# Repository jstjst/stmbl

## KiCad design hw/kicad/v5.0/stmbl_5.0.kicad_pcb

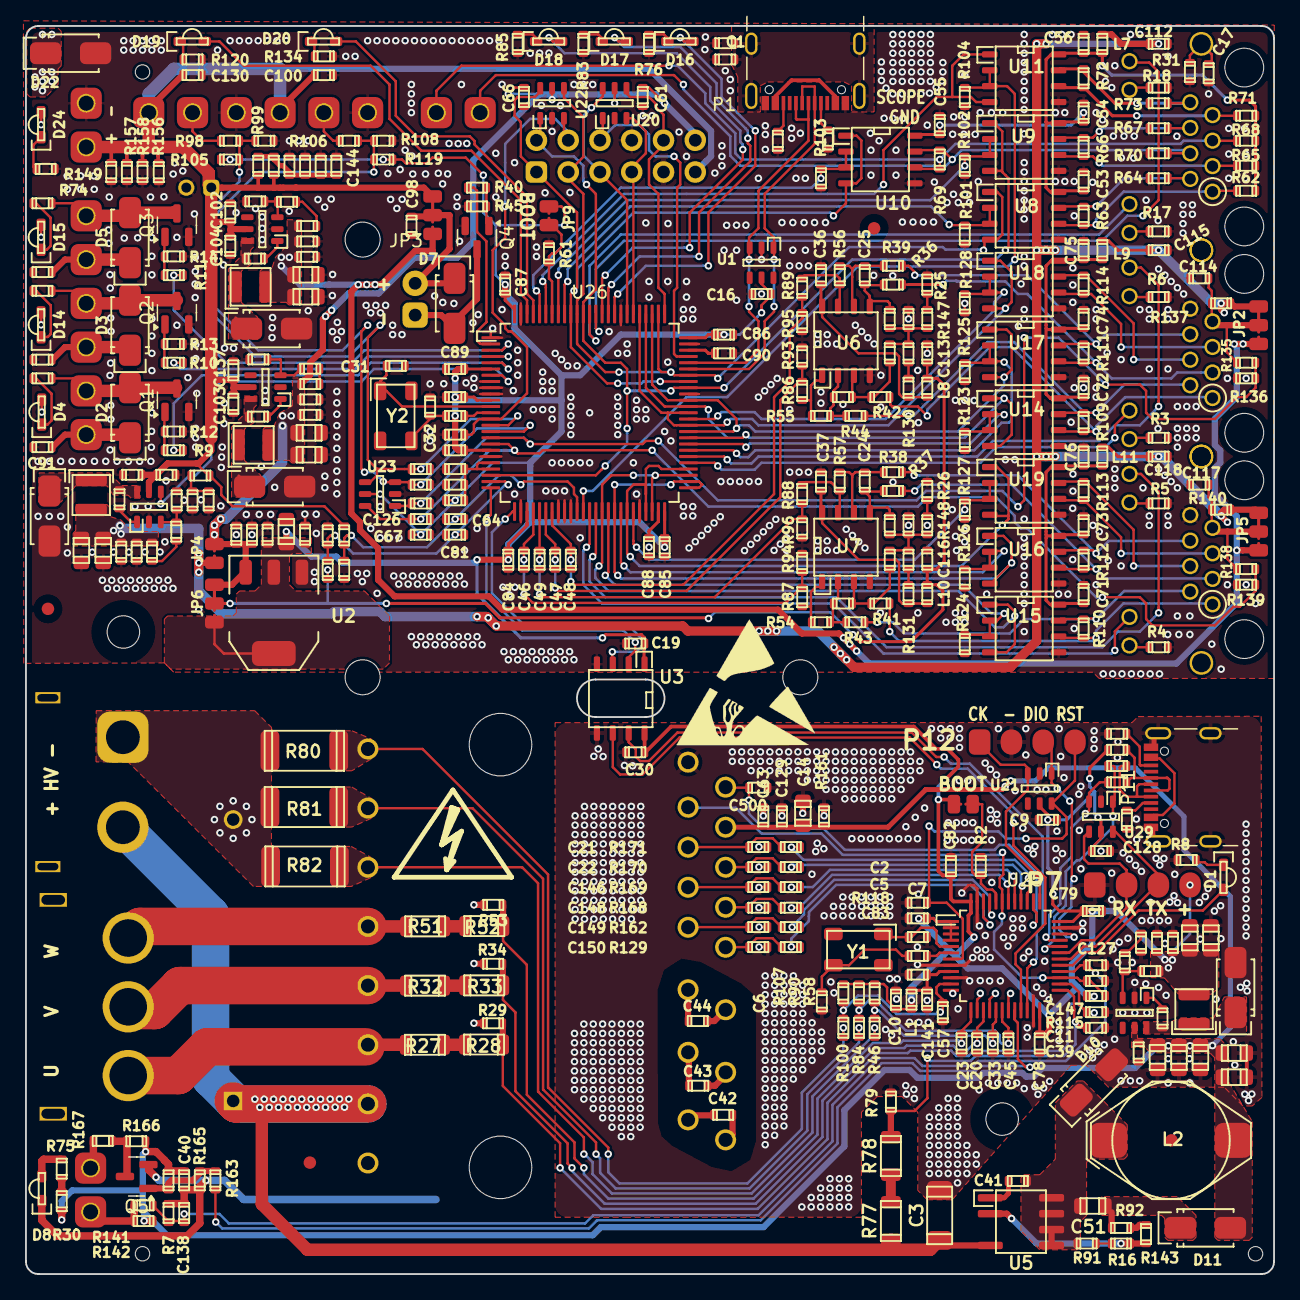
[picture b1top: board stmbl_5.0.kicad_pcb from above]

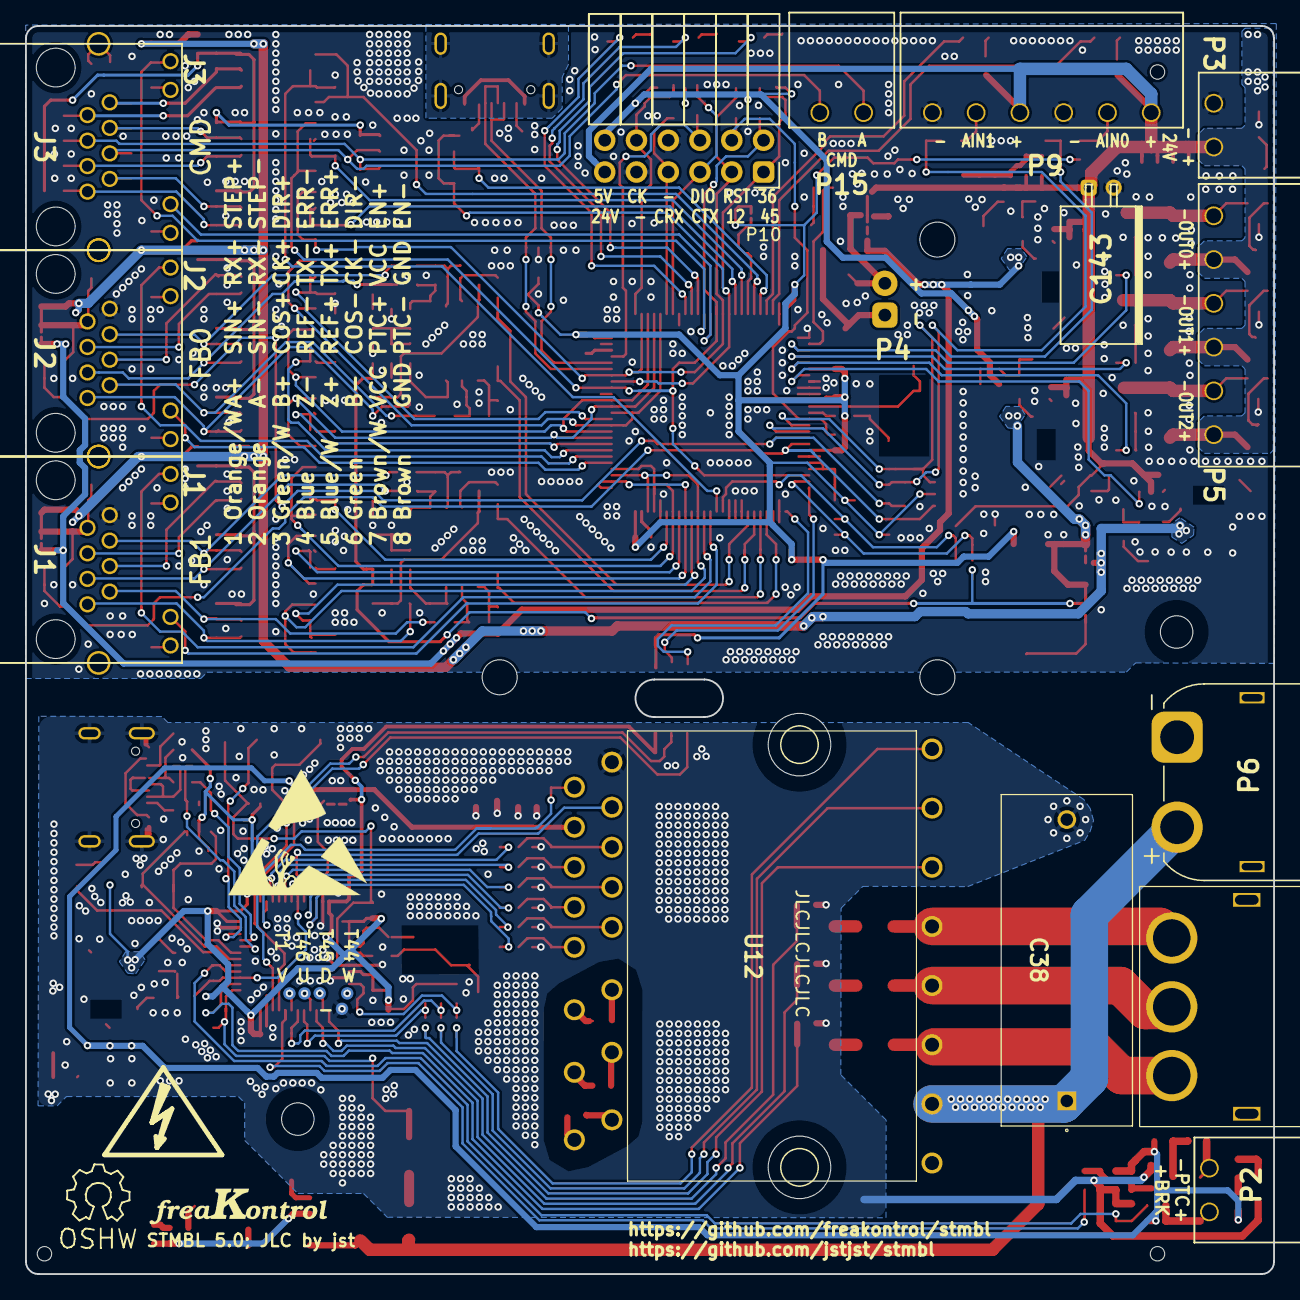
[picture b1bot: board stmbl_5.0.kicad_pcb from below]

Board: 2 copper layers, 99.8 x 99.8 mm, 425 parts (23 on the bottom side), 243 nets.

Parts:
C1, C2, C7, C9, C10, C12, C13, C15, C16, C17, C19, C29, C30, C36, C37, C40, C41, C53, C54, C55, C56, C58, C60, C61, C63, C66, C67, C71, C72, C73, C74, C75, C76, C77, C78, C79, C80, C82, C83, C84, C85, C86, C87, C89, C91, C94, C95, C96, C98, C99, C100, C103, C104, C105, C106, C107, C108, C112, C113, C114, C115, C116, C117, C118, C119, C120, C121, C122, C125, C126, C127, C128, C130, C138: 100n; C_0603
C3: 150n; C_1808
C4, C14, C35, C51, C68, C69, C70, C97, C109, C110, C111, C123, C124, C131, C132, C145: 10µ; C_0805
C5, C6, C11, C20, C23, C24, C25, C26, C27, C31, C32, C33, C39, C45, C57: 18p; C_0603
C8, C18, C42, C43, C44, C50, C62, C65, C88, C90, C101, C102, C129, C133, C134, C135, C136, C137, C139, C140, C141, C142, C144: 2.2µ; C_0603
C21, C22, C46, C47, C48, C49, C52, C59, C64, C81, C146, C147, C148, C149, C150, C500: 1n; C_0603
C38: 680n; potential_snubber01
C143: 22µ; C_Radial_D6.5_L11_P2.5
D1, D16: red; LED-0805-SIDE
D2, D3, D5, D7, D10, D11: ES1J R2; SMA_Standard
D4, D8, D14, D15, D18, D19, D20, D24: green; LED-0805-SIDE
D6, D9, D12, D13: SS34A; SMA_Standard
D17: yellow; LED-0805-SIDE
D22: SMAJ24A TVS 24V; SMA_Standard
J1, J2, J3: RJ45_LED
JP1, JP4, JP9: Jumper_NO_Small; SOLDER_JUMPER
JP2, JP3, JP5, JP6: JUMPER3_NC; SOLDER_JUMPER_3_NC
L1, L3, L7, L8, L9, L10, L11: 220r 700mA; R_0603
L2: 1m 250mA; NPI31W
L4: 4.7µH; SMD_INDUCTOR_32x25
L5, L12: 6.8µH; SMD_INDUCTOR_32x25
L6: 10µH 1A; SMD_INDUCTOR_32x25
LOGO1: OPEN_HARDWARE_1; Symbol_OSHW-Logo_SilkScreen
LOGO2: LOGO; Logo_Freakontrol_1
P1, P11: USB_C_Receptacle_USB2.0; USB_C_Receptacle_GCT_USB4105-xx-A_16P_TopMnt_Horizontal
P2, P3, P15: CONN_01X02; RM3.5_1x2
P4: CONN_01X02; Pin_Header_Angled_1x02
P5, P9: CONN_01X06; RM3.5_1x6
P6: CONN_01X02; AMASS_XT60IPW-M_1x03_P7.20mm_Horizontal
P7, P12: CONN_01X04; Pin_Header_Straight_1x04_smd
P8: CONN_01X03; AMASS Connector MT60_1
P10: CONN_02X06; Socket_Strip_Angled_2x06
Q1, Q2, Q3, Q4, Q5: IRLML6344; SOT-23
R1, R23, R24, R25, R26, R31, R109, R110, R111, R112, R113, R114, R130, R131: 120; R_0603
R2, R12, R13, R14, R15, R16, R30, R45, R61, R63, R66, R69, R72, R75, R91, R99, R101, R102, R103, R104, R105, R108, R117, R118, R119, R121, R122, R123, R124, R125, R126, R127, R128, R136, R139, R153, R165: 1k; R_0603
R3, R4, R5, R6, R8, R17, R18, R46, R76, R83, R84, R85, R93, R94, R95, R96, R100, R120, R134: 470; R_0603
R7, R35, R36, R37, R38, R39, R41, R42, R43, R44, R62, R64, R65, R67, R68, R70, R71, R73, R98, R106, R116, R132, R135, R137, R138, R140, R142, R155, R156, R157, R158: 10k; R_0603
R9, R10, R11, R40, R86, R87, R88, R89, R147, R148, R154, R159, R160, R163, R167, R175, R176: 22; R_0603
R19, R47, R48, R49, R50, R54, R55, R56, R57, R58, R90, R92, R107: 15k; R_0603
R20, R22, R29, R34, R53, R59, R74, R79, R115, R149, R161, R164, R166: 3.9k; R_0603
R21, R60, R97, R133, R141: 51k; R_0603
R27, R28, R32, R33, R51, R52, R77, R78: 249k; R_1206
R80, R81, R82: 0.002; R_2512
R129, R162, R168, R169, R170, R171: 100; R_0603
R143, R145, R174: 1.5k; R_0603
R144, R146, R152, R172, R173, R177: 5.1k; R_0603
REF1, REF3, REF4: Fiducial_1mm_Dia_2.54mm_Outer_CopperTop; Fiducial_1mm_Outer_CopperTop
T1, T2, T44, T45, T46: testpoint; Measurement_Point_Round-SMD-Pad_Small
U1, U20, U21, U22, U23, U29: USBLC6-4SC6; SOT-23-6
U2: zldo1117; SOT-223
U3: SI8621; SOIC-8-N
U4, U13, U24, U28: RT8259; SOT-23-6
U5: LNK304D; SOIC-7
U6, U7: LM358; SOIC-8-N
U8, U9, U10, U11, U14, U15, U16, U17, U18, U19: SN65176B; SOIC-8-N
U12: IKCM30F60GAXKMA1; IKCM30F60GAXKMA1_2
U25: STM32F303CBTx; LQFP-48_7x7mm_Pitch0.5mm
U26: STM32F405VG; LQFP-100_14x14mm_Pitch0.5mm
U234: fan; radial fan
Y1, Y2: 8M; Crystal_SMD_0503_4Pads

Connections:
+3.3VP: C2.1, C4.1, C9.1, C10.2, C30.2, C35.1, C50.1, C60.1, C78.2, C79.2, C82.2, C128.1, JP1.1, L1.2, L4.2, P7.4, R21.1, R58.2, R90.2, R107.2, R115.1, R174.2, U3.8 (VDD2), U21.5 (VBUS), U25.1 (VBAT), U25.2 (PC13), U25.3 (PC14), U25.4 (PC15), U25.24 (VDD), U25.36 (VDD), U25.48 (VDD), U29.5 (VBUS)
+3V3: C16.2, C18.1, C19.1, C67.1, C77.2, C80.2, C84.2, C85.2, C86.2, C87.2, C89.2, C99.1, C131.1, JP6.3, JP9.1, L3.2, R105.1, R119.1, U1.5 (VBUS), U2.2 (VO), U3.1 (VDD1), U23.5 (VBUS), U26.6 (VBAT), U26.11 (VDD), U26.19 (VDD), U26.28 (VDD), U26.50 (VDD), U26.75 (VDD), U26.100 (VDD)
+5F: C112.1, C115.2, C118.2, C122.1, C123.1, C124.1, C134.1, JP2.1, JP4.1, JP5.1, L7.2, L9.1, L11.1, L12.2, R137.2, R140.2, R144.1
+5V: C8.1, C61.1, C66.1, C96.1, C107.1, C109.1, C111.1, C135.1, JP4.2, JP6.1, L5.2, P10.12, R145.1, U2.3 (VI), U20.5 (VBUS), U22.5 (VBUS)
+5VA: C113.2, C116.2, JP6.2, L8.1, L10.1, R121.1
+12V: C108.1, C110.1, C132.1, C136.1, JP2.3, JP3.3, JP5.3, L6.2, R146.1
+15V: C14.2, C40.2, C58.1, C63.1, C68.1, C69.1, C70.1, C97.1, C129.1, C145.1, D11.2 (A), L2.2, R30.1, R142.1, R161.1, R164.1, R166.1, U4.5 (VIN), U12.13 (VDD)
+24V: C91.1, C94.1, C95.1, C100.1, C102.1, C103.1, C104.1, C120.1, C130.1, C133.1, C137.1, C143.1, D2.1 (K), D3.1 (K), D4.2 (A), D5.1 (K), D14.2 (A), D15.2 (A), D22.1 (K), D24.2 (A), JP3.1, P3.1, P5.1, P5.3, P5.5, P9.1, P9.4, P10.11, R116.1, R154.1, R155.1, R156.1, R157.1, R158.1, R159.1, R160.1, U13.5 (VIN), U24.5 (VIN), U28.5 (VIN)
/ctrl/CMD/D12: P10.3, U8.1 (RO), U8.4 (DI), U22.4 (I/O3), U26.69 (PA10/USART1_RX/TIM1_CH3/OTG_FS_ID/EVENT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), U26.77 (PA15/JTDI/SPI3_NSS/I2S3_WS/TIM2_CH1_ETR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), U26.90 (PB4/NJTRST/SPI3_MISO/TIM3_CH1/SPI1_MISO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)
/ctrl/CMD/D36: P10.2, U9.1 (RO), U9.4 (DI), U22.1 (I/O1), U26.23 (PA0/WKUP/USART2_CTS/UART4_TX/TIM2_CH1_E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), U26.67 (PA8/MCO1/USART1_CK/TIM1_CH1/I2C3_SCL/OT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), U26.89 (PB3/JTDO/TRACESWO/SPI3_SCK/I2S3_CK/TIM2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)
/ctrl/CMD/D45: P10.1, U10.1 (RO), U10.4 (DI), U22.6 (I/O4), U26.68 (PA9/USART1_TX/TIM1_CH2/I2C3_SMBA/EVENTO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), U26.91 (PB5/I2C1_SMBA/CAN2_RX/OTG_HS_ULPI_D7/TI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)
/ctrl/CMD/D78: U11.1 (RO), U11.4 (DI), U26.95 (PB8/TIM4_CH3/SDIO_D4/TIM10_CH1/I2C1_SCL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)
/ctrl/CMD/E12: R101.1, U8.2 (~RE), U8.3 (DE), U26.92 (PB6/I2C1_SCL/TIM4_CH1/CAN2_TX/USART1_TX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)
/ctrl/CMD/E36: R102.1, U9.2 (~RE), U9.3 (DE), U26.93 (PB7/I2C1_SDA/FSMC_NL/USART1_RX/TIM4_CH2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)
/ctrl/CMD/E45: R103.1, U10.2 (~RE), U10.3 (DE), U26.96 (PB9/SPI2_NSS/I2S2_WS/TIM4_CH4/TIM11_CH1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)
/ctrl/CMD/E78: R104.1, U11.2 (~RE), U11.3 (DE), U26.37 (PB2/BOOT1/EVENTOUT)
/ctrl/CMD/L1: J3.12, U26.88 (PD7/USART2_CK/FSMC_NE1/FSMC_NCE2/EVENTO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)
/ctrl/CMD/L2: J3.10, U26.87 (PD6/FSMC_NWAIT/USART2_RX/EVENTOUT)
/ctrl/FB0/A12: C47.1, R86.1, R93.1, U26.31 (PA6/SPI1_MISO/TIM8_BKIN/TIM13_CH1/TIM3_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)
/ctrl/FB0/A35: C48.1, R89.1, R95.1, U26.32 (PA7/SPI1_MOSI/TIM8_CH1N/TIM14_CH1/TIM3_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)
/ctrl/FB0/A78: C125.1, R135.2, R136.1, U23.1 (I/O1), U26.17 (PC2/SPI2_MISO/OTG_HS_ULPI_DIR/I2S2ext_S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)
/ctrl/FB0/D12: U14.1 (RO), U14.4 (DI), U26.59 (PD12/FSMC_ALE/FSMC_A17/TIM4_CH1/USART3_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), U26.64 (PC7/I2S3_MCK/TIM8_CH2/SDIO_D7/USART6_RX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), U26.79 (PC11/UART4_RX/SPI3_MISO/SDIO_D3/USART3_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)
/ctrl/FB0/D36: U17.1 (RO), U17.4 (DI), U26.60 (PD13/FSMC_A18/TIM4_CH2/EVENTOUT), U26.65 (PC8/TIM8_CH3/SDIO_D0/TIM3_CH3/USART6_CK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), U26.78 (PC10/SPI3_SCK/I2S3_CK/UART4_TX/SDIO_D2/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)
/ctrl/FB0/D45: U18.1 (RO), U18.4 (DI), U26.61 (PD14/FSMC_D0/TIM4_CH3/EVENTOUT/_EVENTOUT), U26.63 (PC6/I2S2_MCK/TIM8_CH1/SDIO_D6/USART6_TX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), U26.80 (PC12/UART5_TX/SDIO_CK/SPI3_MOSI/I2S3_SD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)
/ctrl/FB0/E12: R123.1, U14.2 (~RE), U14.3 (DE), U26.58 (PD11/FSMC_CLE/FSMC_A16/USART3_CTS/EVENT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)
/ctrl/FB0/E36: R125.1, U17.2 (~RE), U17.3 (DE), U26.57 (PD10/FSMC_D15/USART3_CK/EVENTOUT)
/ctrl/FB0/E45: R128.1, U18.2 (~RE), U18.3 (DE), U26.62 (PD15/FSMC_D1/TIM4_CH4/EVENTOUT)
/ctrl/FB0/L1: J2.12, U26.55 (PD8/FSMC_D13/USART3_TX/EVENTOUT)
/ctrl/FB0/L2: J2.10, U26.56 (PD9/FSMC_D14/USART3_RX/EVENTOUT)
/ctrl/FB1/A12: C46.1, R87.1, R94.1, U26.29 (PA4/SPI1_NSS/SPI3_NSS/USART2_CK/OTG_HS_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)
/ctrl/FB1/A35: C49.1, R88.1, R96.1, U26.30 (PA5/SPI1_SCK/OTG_HS_ULPI_CK/TIM2_CH1_ET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)
/ctrl/FB1/A78: C126.1, R138.2, R139.1, U23.6 (I/O4), U26.18 (PC3/SPI2_MOSI/I2S2_SD/OTG_HS_ULPI_NXT/E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)
/ctrl/FB1/D12: U15.1 (RO), U15.4 (DI), U26.40 (PE9/FSMC_D6/TIM1_CH1/EVENTOUT), U26.48 (PB11/I2C2_SDA/USART3_RX/OTG_HS_ULPI_D4/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), U26.53 (PB14/SPI2_MISO/TIM1_CH2N/TIM12_CH1/OTG_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)
/ctrl/FB1/D36: U16.1 (RO), U16.4 (DI), U26.42 (PE11/FSMC_D8/TIM1_CH2/EVENTOUT), U26.51 (PB12/SPI2_NSS/I2S2_WS/I2C2_SMBA/USART3_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), U26.52 (PB13/SPI2_SCK/I2S2_CK/USART3_CTS/TIM1_C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)
/ctrl/FB1/D45: U19.1 (RO), U19.4 (DI), U26.44 (PE13/FSMC_D10/TIM1_CH3/EVENTOUT), U26.47 (PB10/SPI2_SCK/I2S2_CK/I2C2_SCL/USART3_T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), U26.54 (PB15/SPI2_MOSI/I2S2_SD/TIM1_CH3N/TIM8_C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)
/ctrl/FB1/E12: R124.1, U15.2 (~RE), U15.3 (DE), U26.41 (PE10/FSMC_D7/TIM1_CH2N/EVENTOUT)
/ctrl/FB1/E36: R126.1, U16.2 (~RE), U16.3 (DE), U26.43 (PE12/FSMC_D9/TIM1_CH3N/EVENTOUT)
/ctrl/FB1/E45: R127.1, U19.2 (~RE), U19.3 (DE), U26.45 (PE14/FSMC_D11/TIM1_CH4/EVENTOUT)
/ctrl/FB1/L1: J1.12, U26.38 (PE7/FSMC_D4/TIM1_ETR/EVENTOUT)
/ctrl/FB1/L2: J1.10, U26.39 (PE8/FSMC_D5/TIM1_CH1N/EVENTOUT)
/ctrl/IO/CAN_RX: P10.7, U20.3 (I/O2), U26.81 (PD0/FSMC_D2/CAN1_RX/EVENTOUT)
/ctrl/IO/CAN_TX: P10.5, U20.6 (I/O4), U26.82 (PD1/FSMC_D3/CAN1_TX/EVENTOUT)
/ctrl/IO/IO_FAN: R40.2, U26.2 (PE3/TRACED0/FSMC_A19/EVENTOUT)
/ctrl/IO/IO_GREEN: D18.2 (A), U26.86 (PD5/FSMC_NWE/USART2_TX/EVENTOUT)
/ctrl/IO/IO_IN0: C52.1, R98.2, R99.1, R105.2, U23.4 (I/O3), U26.15 (PC0/OTG_HS_ULPI_STP/EVENTOUT)
/ctrl/IO/IO_IN1: C59.1, R106.2, R108.1, R119.2, U23.3 (I/O2), U26.16 (PC1/_EVENTOUT)
/ctrl/IO/IO_L0: D19.2 (A), U26.98 (PE1/FSMC_NBL1/EVENTOUT)
/ctrl/IO/IO_L1: D20.2 (A), U26.97 (PE0/TIM4_ETR/FSMC_NBL0/EVENTOUT)
/ctrl/IO/IO_OUT0: R11.2, U26.3 (PE4/TRACED1/FSMC_A20/EVENTOUT)
/ctrl/IO/IO_OUT1: R10.2, U26.4 (PE5/TRACED2/FSMC_A21/TIM9_CH1/EVENTOUT)
/ctrl/IO/IO_OUT2: R9.2, U26.5 (PE6/TRACED3_/_FSMC_A22/TIM9_CH2/EVENTOUT)
/ctrl/IO/IO_RED: D16.2 (A), U26.84 (PD3/FSMC_CLK/USART2_CTS/EVENTOUT)
/ctrl/IO/IO_YELLOW: D17.2 (A), U26.85 (PD4/FSMC_NOE/USART2_RTS/EVENTOUT)
/ctrl/IO/NRST: C29.2, P10.4, U22.3 (I/O2), U26.14 (NRST)
/ctrl/IO/SWCK: P10.10, U20.4 (I/O3), U26.76 (PA14/JTCK/SWCLK/EVENTOUT)
/ctrl/IO/SWDIO: P10.6, U20.1 (I/O1), U26.72 (PA13/JTMS/SWDIO/EVENTOUT)
/ctrl/RX: U3.3 (A2), U26.26 (PA3/USART2_RX/TIM5_CH4/TIM9_CH2/TIM2_CH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)
/ctrl/TX: U3.2 (A1), U26.25 (PA2/USART2_TX/TIM5_CH3/TIM9_CH1/TIM2_CH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)
/ctrl/f4/A_5V: C81.1, R121.2, R122.1, U26.24 (PA1/USART2_RTS/UART4_RX/TIM5_CH2/TIMM2_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)
/ctrl/f4/A_24V: C64.1, R116.2, R117.1, U26.36 (PB1/TIM3_CH4/TIM8_CH3N/OTG_HS_ULPI_D2/O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)
/ctrl/f4/EN_5V: U26.7 (PC13/EVENTOUT), U28.4 (EN)
/ctrl/f4/shield: C1.1, P1.S1 (SHIELD), R1.1
/hv/back-emf/HV_: C39.1, R78.2, R79.1, U25.25 (PB12)
/hv/back-emf/U: P8.3, R27.1, U12.22 (U)
/hv/back-emf/U_: C11.1, R28.2, R29.1, U25.26 (PB13)
/hv/back-emf/V: P8.2, R32.1, U12.21 (V)
/hv/back-emf/V_: C20.1, R33.2, R34.1, U25.15 (PA5)
/hv/back-emf/W: P8.1, R51.1, U12.20 (W)
/hv/back-emf/W_: C23.1, R52.2, R53.1, U25.13 (PA3)
/hv/cur/A_IU: C33.1, R46.1, R58.1, U25.17 (PA7)
/hv/cur/A_IV: C45.1, R84.1, R90.1, U25.18 (PB0)
/hv/cur/A_IW: C57.1, R100.1, R107.1, U25.11 (PA1)
/hv/cur/IU: R46.2, R82.1, U12.19 (NU)
/hv/cur/IV: R81.1, R84.2, U12.18 (NV)
/hv/cur/IW: R80.1, R100.2, U12.17 (NW)
/hv/driver/HU: R129.1, U25.46 (PB9)
/hv/driver/HV: R162.1, U25.45 (PB8)
/hv/driver/HW: R168.1, U25.42 (PB6)
/hv/driver/LU: R169.1, U25.41 (PB5)
/hv/driver/LV: R170.1, U25.40 (PB4)
/hv/driver/LW: R171.1, U25.39 (PB3)
/hv/driver/Vth: C147.1, R115.2, U12.14 (VFO), U25.27 (PB14), U25.43 (PB7)
/hv/driver/itrip: C500.1, U12.15 (ITRIP), U25.38 (PA15)
/hv/f3/A_T_MOT: C127.2, C138.2, R7.2, R141.2, U25.28 (PB15)
/hv/f3/BRK: R163.1, U25.20 (PB2)
/hv/f3/HV_RX: U3.7 (B1), U25.22 (PB11)
/hv/f3/HV_TX: U3.6 (B2), U25.21 (PB10)
/hv/f3/IO_RX: P7.2, U25.31 (PA10), U29.4 (I/O3)
/hv/f3/IO_TX: P7.3, U25.30 (PA9), U29.6 (I/O4)
/hv/f3/NRST: C7.1, P12.4, U21.6 (I/O4), U25.7 (NRST)
/hv/f3/SWCLK: P12.1, U21.3 (I/O2), U25.37 (PA14)
/hv/f3/SWDIO: P12.3, U21.1 (I/O1), U25.34 (PA13)
/hv/f3/USB_DM: R175.1, U25.32 (PA11), U29.1 (I/O1)
/hv/f3/USB_DP: R176.1, U25.33 (PA12), U29.3 (I/O2)
GND: C1.2, C8.2, C12.2, C13.2, C16.1, C17.2, C18.2, C19.2, C29.1, C31.2, C32.2, C36.1, C37.1, C46.2, C47.2, C48.2, C49.2, C52.2, C53.2, C54.2, C55.2, C56.2, C59.2, C61.2, C62.2, C64.2, C65.1, C66.2, C67.2, C71.2, C72.2, C73.2, C74.2, C75.2, C76.2, C77.1, C80.1, C81.2, C84.1, C85.1, C86.1, C87.1, C88.2, C89.1, C90.2, C91.2, C94.2, C95.2, C96.2, C98.2, C99.2, C100.2, C101.2, C102.2, C103.2, C104.2, C107.2, C108.2, C109.2, C110.2, C111.2, C112.2, C113.1, C114.2, C115.1, C116.1, C117.2, C118.1, C119.1, C120.2, C122.2, C123.2, C124.2, C125.2, C126.2, C130.2, C131.2, C132.2, C133.2, C134.2, C135.2, C136.2, C137.2, C139.2, C140.2, C142.2, C143.2, C144.2, D9.2 (A), D12.2 (A), D13.2 (A), D22.2 (A), J1.8, J2.8, P1.A1 (GND), P1.A12 (GND), P1.B1 (GND), P1.B12 (GND), P3.2, P9.3, P9.6, P10.8, P10.9, Q1.2 (S), Q2.2 (S), Q3.2 (S), Q4.2 (S), R1.2, R3.2, R4.2, R5.2, R6.2, R12.2, R13.2, R14.2, R17.2, R18.2, R25.2, R26.2, R31.2, R35.2, R45.2, R59.2, R61.1, R64.2, R67.2, R70.2, R73.2, R76.2, R83.2, R85.2, R93.2, R94.2, R95.2, R96.2, R99.2, R101.2, R102.2, R103.2, R104.2, R108.2, R117.2, R120.2, R122.2, R123.2, R124.2, R125.2, R126.2, R127.2, R128.2, R132.2, R134.2, R136.2, R139.2, R149.2, R152.1, R155.2, R156.2, R157.2, R158.2, R177.1, U1.2 (GND), U2.1 (GND), U3.4 (GND1), U6.4 (V-), U7.4 (V-), U8.5 (GND), U9.5 (GND), U10.5 (GND), U11.5 (GND), U13.2 (GND), U14.5 (GND), U15.5 (GND), U16.5 (GND), U17.5 (GND), U18.5 (GND), U19.5 (GND), U20.2 (GND), U22.2 (GND), U23.2 (GND), U24.2 (GND), U26.1 (PE2/TRACECLK/FSMC_A23/EVENTOUT), U26.8 (PC14/OSC32_IN/EVENTOUT), U26.9 (PC15/OSC32_OUT/EVENTOUT), U26.10 (VSS), U26.20 (VSSA), U26.27 (VSS), U26.33 (PC4/EVENTOUT), U26.34 (PC5/EVENTOUT), U26.35 (PB0/TIM3_CH3/TIM8_CH2N/OTG_HS_ULPI_D1/T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), U26.46 (PE15/FSMC_D12/TIM1_BKIN/EVENTOUT), U26.66 (PC9/I2S_CKIN/MCO2/TIM8_CH4/SDIO_D1/I2C3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), U26.74 (VSS), U26.83 (PD2/TIM3_ETR/UART5_RX/SDIO_CMD/EVENTOUT), U26.99 (VSS), U28.2 (GND)
GNDD: C17.1, J1.13, J2.13, J3.13, R31.1
GNDPWR: C2.2, C3.2, C4.2, C5.2, C6.2, C7.2, C9.2, C10.1, C11.2, C14.1, C20.2, C21.2, C22.2, C23.2, C30.1, C33.2, C35.2, C38.2, C39.2, C40.1, C45.2, C50.2, C57.2, C58.2, C60.2, C63.2, C68.2, C69.2, C70.2, C78.1, C79.1, C82.1, C83.1, C97.2, C127.1, C128.2, C129.2, C138.1, C141.1, C145.2, C146.2, C147.2, C148.2, C149.2, C150.2, C500.2, D6.2 (A), D8.1 (K), D10.2 (A), P6.1, P7.1, P11.A1 (GND), P11.A12 (GND), P11.B1 (GND), P11.B12 (GND), P11.S1 (SHIELD), P12.2, Q5.2 (S), R2.2, R7.1, R8.1, R15.2, R29.2, R34.2, R53.2, R79.2, R80.2, R81.2, R82.2, R161.2, R165.2, R172.1, R173.1, T2.1, U3.5 (GND2), U4.2 (GND), U12.16 (VSS), U21.2 (GND), U25.8 (VSSA), U25.10 (PA0), U25.23 (VSS), U25.35 (VSS), U25.47 (VSS), U29.2 (GND)
unnamed: C6.1, R118.2, Y1.2
unnamed: C12.1, R23.2, R48.1, R49.1, R148.1
unnamed: C13.1, R24.2, R47.1, R50.1, R147.1
unnamed: C32.1, R153.2, Y2.2
unnamed: C62.1, C101.1, R159.2
unnamed: C114.1, J2.7, JP2.2, R135.1, R137.1
unnamed: C117.1, J1.7, JP5.2, R138.1, R140.1
unnamed: C139.1, C140.1, C142.1, C144.1, R154.2, R160.2
unnamed: D1.2 (A), U25.29 (PA8)
unnamed: D1.1 (K), R8.2
unnamed: D2.2 (A), P5.2, Q1.3 (D), R20.2
unnamed: D3.2 (A), P5.4, Q2.3 (D), R22.2
unnamed: D4.1 (K), R20.1
unnamed: D5.2 (A), P5.6, Q3.3 (D), R74.2
unnamed: C15.2, D6.1 (K), L4.1, U4.6 (PH)
unnamed: D7.2 (A), P4.1, Q4.3 (D)
unnamed: C98.1, D7.1 (K), JP3.2, P4.2
unnamed: D8.2 (A), R75.2
unnamed: C105.2, D9.1 (K), L5.1, U13.6 (PH)
unnamed: C41.2, C51.2, D10.1 (K), L2.1, R91.1, U5.5 (S), U5.6 (S), U5.7 (S), U5.8 (S)
unnamed: C51.1, D11.1 (K), R92.2
unnamed: C106.2, D12.1 (K), L6.1, U24.6 (PH)
unnamed: C121.2, D13.1 (K), L12.1, U28.6 (PH)
unnamed: D14.1 (K), R22.1
unnamed: D15.1 (K), R74.1
unnamed: D16.1 (K), R76.1
unnamed: D17.1 (K), R83.1
unnamed: D18.1 (K), R85.1
unnamed: D19.1 (K), R120.1
unnamed: D20.1 (K), R134.1
unnamed: D24.1 (K), R149.1
unnamed: J1.9, R5.1
unnamed: J1.11, R4.1
unnamed: J2.9, R6.1
unnamed: J2.11, R3.1
unnamed: J3.9, R18.1
unnamed: J3.11, R17.1
unnamed: P1.A5 (CC1), R152.2
unnamed: P1.B5 (CC2), R177.2
unnamed: P1.A4 (VBUS), P1.A9 (VBUS), P1.B4 (VBUS), P1.B9 (VBUS)
unnamed: P2.1, R141.1, R142.2
unnamed: P2.2, R167.2
unnamed: P9.2, R98.1
unnamed: P9.5, R106.1
unnamed: P11.A5 (CC1), R172.2
unnamed: P11.B5 (CC2), R173.2
unnamed: P11.A6 (D+), P11.B6 (D+), R174.1, R176.2
unnamed: P11.A7 (D-), P11.B7 (D-), R175.2
unnamed: P11.A4 (VBUS), P11.A9 (VBUS), P11.B4 (VBUS), P11.B9 (VBUS)
unnamed: J3.5, P15.1, R68.2, R69.1, U10.6 (A)
unnamed: J3.4, P15.2, R69.2, R70.1, U10.7 (B)
unnamed: Q1.1 (G), R9.1, R12.1
unnamed: Q2.1 (G), R10.1, R13.1
unnamed: Q3.1 (G), R11.1, R14.1
unnamed: Q4.1 (G), R40.1, R45.1
unnamed: Q5.3 (D), R166.2, R167.1
unnamed: Q5.1 (G), R163.2, R164.2, R165.1
unnamed: R15.1, R19.2
unnamed: R16.1, R91.2
unnamed: R27.2, R28.1
unnamed: R30.2, R75.1
unnamed: R32.2, R33.1
unnamed: R51.2, R52.1
unnamed: R54.1, R87.2, U7.1
unnamed: R55.1, R86.2, U6.1
unnamed: R56.1, R89.2, U6.7
unnamed: R57.1, R88.2, U7.7
unnamed: R77.2, R78.1
unnamed: R24.1, R130.2
unnamed: R23.1, R131.2
unnamed: R133.1, R144.2
unnamed: R92.1, R143.2
unnamed: R60.1, R145.2
unnamed: R97.1, R146.2
unnamed: R25.1, R147.2
unnamed: R26.1, R148.2
unnamed: P1.A7 (D-), P1.B7 (D-), U1.1 (I/O1), U26.70 (PA11/USART1_CTS/CAN1_RX/TIM1_CH4_/OTG_F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)
unnamed: P1.A6 (D+), P1.B6 (D+), U1.3 (I/O2), U26.71 (PA12/USART1_RTS/CAN1_TX/TIM1_ETR/OTG_FS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)
unnamed: C15.1, U4.1 (BST)
unnamed: R19.1, R21.2, U4.3 (FB)
unnamed: C41.1, U5.1 (BP)
unnamed: R16.2, R143.1, U5.2 (FB)
unnamed: C27.1, R42.1, R47.2, U6.3 (+)
unnamed: C27.2, R44.1, R55.2, U6.2 (-)
unnamed: C25.1, R36.1, R50.2, U6.5 (+)
unnamed: C25.2, R39.1, R56.2, U6.6 (-)
unnamed: C36.2, L8.2, R130.1, U6.8 (V+)
unnamed: C26.1, R41.1, R48.2, U7.3 (+)
unnamed: C26.2, R43.1, R54.2, U7.2 (-)
unnamed: C24.1, R37.1, R49.2, U7.5 (+)
unnamed: C24.2, R38.1, R57.2, U7.6 (-)
unnamed: C37.2, L10.2, R131.1, U7.8 (V+)
unnamed: J3.1, R62.2, R63.1, U8.6 (A)
unnamed: J3.2, R63.2, R64.1, U8.7 (B)
unnamed: J3.3, R65.2, R66.1, U9.6 (A)
unnamed: J3.6, R66.2, R67.1, U9.7 (B)
unnamed: C53.1, C54.1, C55.1, C56.1, L7.1, R62.1, R65.1, R68.1, R71.1, U8.8 (VCC), U9.8 (VCC), U10.8 (VCC), U11.8 (VCC)
unnamed: J3.7, R71.2, R72.1, U11.6 (A)
unnamed: J3.8, R72.2, R73.1, U11.7 (B)
unnamed: C150.1, R129.2, U12.7 (HIN(U))
unnamed: C149.1, R162.2, U12.8 (HIN(V))
unnamed: C148.1, R168.2, U12.9 (HIN(W))
unnamed: C146.1, R169.2, U12.10 (LIN(U))
unnamed: C22.1, R170.2, U12.11 (LIN(V))
unnamed: C21.1, R171.2, U12.12 (LIN(W))
unnamed: C42.1, U12.2 (VB(U))
unnamed: C43.1, U12.4 (VB(V))
unnamed: C44.1, U12.6 (VB(W))
unnamed: C42.2, U12.1 (VS(U))
unnamed: C43.2, U12.3 (VS(V))
unnamed: C44.2, U12.5 (VS(W))
unnamed: C105.1, U13.1 (BST)
unnamed: R35.1, R60.2, U13.3 (FB)
unnamed: J2.1, R42.2, R109.1, U14.6 (A)
unnamed: J2.2, R44.2, R109.2, U14.7 (B)
unnamed: C72.1, C74.1, C75.1, L9.2, U14.8 (VCC), U17.8 (VCC), U18.8 (VCC)
unnamed: J1.1, R41.2, R110.1, U15.6 (A)
unnamed: J1.2, R43.2, R110.2, U15.7 (B)
unnamed: C71.1, C73.1, C76.1, L11.2, U15.8 (VCC), U16.8 (VCC), U19.8 (VCC)
unnamed: J1.3, R37.2, R112.1, U16.6 (A)
unnamed: J1.6, R38.2, R112.2, U16.7 (B)
unnamed: J2.3, R36.2, R111.1, U17.6 (A)
unnamed: J2.6, R39.2, R111.2, U17.7 (B)
unnamed: J2.5, R114.1, U18.6 (A)
unnamed: J2.4, R114.2, U18.7 (B)
unnamed: J1.5, R113.1, U19.6 (A)
unnamed: J1.4, R113.2, U19.7 (B)
unnamed: C106.1, U24.1 (BST)
unnamed: R59.1, R97.2, U24.3 (FB)
unnamed: JP1.2, R2.1, U25.44 (BOOT0)
unnamed: T44.1, U25.12 (PA2)
unnamed: T45.1, U25.14 (PA4)
unnamed: T46.1, U25.16 (PA6)
unnamed: T1.1, U25.19 (PB1)
unnamed: C5.1, U25.5 (PF0), Y1.1
unnamed: R118.1, U25.6 (PF1)
unnamed: C83.2, C141.2, L1.1, U25.9 (VDDA)
unnamed: JP9.2, R61.2, U26.94 (BOOT0)
unnamed: C31.1, U26.12 (PH0/OSC_IN/EVENTOUT), Y2.1
unnamed: R153.1, U26.13 (PH1/OSC_OUT/EVENTOUT)
unnamed: C88.1, U26.49 (VCAP_1)
unnamed: C90.1, U26.73 (VCAP_2)
unnamed: C65.2, C119.2, L3.1, U26.21 (VREF+), U26.22 (VDDA)
unnamed: C121.1, U28.1 (BST)
unnamed: R132.1, R133.2, U28.3 (FB)
VPP: C3.1, C38.1, P6.2, R77.1, U5.4 (D), U12.23

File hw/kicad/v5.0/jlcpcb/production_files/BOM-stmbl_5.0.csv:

Comment,Designator,Footprint,LCSC,Quantity
STM32F303CBTx,U25,LQFP-48_7x7mm_Pitch0.5mm,C108516,1
USBLC6-4SC6,"U1,U20,U21,U22,U23,U29",SOT-23-6,C111212,6
SMAJ24A TVS 24V,D22,SMA_Standard,C113962,1
100n,"C1,C10,C100,C103,C104,C105,C106,C107,C108,C112,C113,C114,C115,C116,C117,C118,C119,C12,C120,C121,C122,C125,C126,C127,C128,C13,C130,C138,C15,C16,C17,C19,C2,C29,C30,C36,C37,C40,C41,C53,C54,C55,C56,C58,C60,C61,C63,C66,C67,C7,C71,C72,C73,C74,C75,C76,C77,C78,C79,C80,C82,C83,C84,C85,C86,C87,C89,C9,C91,C94,C95,C96,C98,C99",C_0603,C14663,74
1n,"C146,C147,C148,C149,C150,C21,C22,C46,C47,C48,C49,C500,C52,C59,C64,C81",C_0603,C1588,16
yellow,D17,LED-0805-SIDE,C160468,1
green,"D14,D15,D18,D19,D20,D24,D4,D8",LED-0805-SIDE,C160469,8
18p,"C11,C20,C23,C24,C25,C26,C27,C31,C32,C33,C39,C45,C5,C57,C6",C_0603,C1647,15
RT8259,"U13,U24,U28,U4",SOT-23-6,C16819,4
LNK304D,U5,SOIC-7,C185829,1
1m 250mA,L2,NPI31W,C2045430,1
0.002,"R80,R81,R82",R_2512,C2090861,3
1k,"R101,R102,R103,R104,R105,R108,R117,R118,R119,R12,R121,R122,R123,R124,R125,R126,R127,R128,R13,R136,R139,R14,R15,R153,R16,R165,R2,R30,R45,R61,R63,R66,R69,R72,R75,R91,R99",R_0603,C21190,37
100,"R129,R162,R168,R169,R170,R171",R_0603,C22775,6
120,"R1,R109,R110,R111,R112,R113,R114,R130,R131,R23,R24,R25,R26,R31",R_0603,C22787,14
15k,"R107,R19,R47,R48,R49,R50,R54,R55,R56,R57,R58,R90,R92",R_0603,C22809,13
1.5k,"R143,R145,R174",R_0603,C22843,3
3.9k,"R115,R149,R161,R164,R166,R20,R22,R29,R34,R53,R59,R74,R79",R_0603,C23018,13
470,"R100,R120,R134,R17,R18,R3,R4,R46,R5,R6,R76,R8,R83,R84,R85,R93,R94,R95,R96",R_0603,C23179,19
5.1k,"R144,R146,R152,R172,R173,R177",R_0603,C23186,6
51k,"R133,R141,R21,R60,R97",R_0603,C23196,5
22,"R10,R11,R147,R148,R154,R159,R160,R163,R167,R175,R176,R40,R86,R87,R88,R89,R9",R_0603,C23345,17
10k,"R106,R116,R132,R135,R137,R138,R140,R142,R35,R36,R37,R38,R39,R41,R42,R43,R44,R62,R64,R65,R67,R68,R7,R70,R71,R73,R98",R_0603,C25804,27
8M,"Y1,Y2",Crystal_SMD_0503_4Pads,C276420,2
red,"D1,D16",LED-0805-SIDE,C284935,2
USB_C_Receptacle_USB2.0,"P1,P11",USB_C_Receptacle_GCT_USB4105-xx-A_16P_TopMnt_Horizontal,C2988369,2
SN65176B,"U10,U11,U14,U15,U16,U17,U18,U19,U8,U9",SOIC-8-N,C31302,10
249k,"R27,R28,R32,R33,R51,R52,R77,R78",R_1206,C322960,8
2.2µ,"C101,C102,C129,C133,C134,C135,C136,C137,C139,C140,C141,C142,C144,C18,C42,C43,C44,C50,C62,C65,C8,C88,C90",C_0603,C377773,23
ES1J R2,"D10,D11,D2,D3,D5,D7",SMA_Standard,C412437,6
zldo1117,U2,SOT-223,C435835,1
10µ,"C109,C110,C111,C123,C124,C131,C132,C14,C145,C35,C4,C51,C68,C69,C70,C97",C_0805,C440198,16
SI8621,U3,SOIC-8-N,C461877,1
IRLML6344,"Q1,Q2,Q3,Q4,Q5",SOT-23,C53550,5
4.7µH,L4,SMD_INDUCTOR_32x25,C5357113,1
STM32F405VG,U26,LQFP-100_14x14mm_Pitch0.5mm,C56621,1
LM358,"U6,U7",SOIC-8-N,C74525,2
SS34A,"D12,D13,D6,D9",SMA_Standard,C8678,4
220r 700mA,"L1,L10,L11,L3,L7,L8,L9",R_0603,C88971,7

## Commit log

2025-01-07 JLCPCB production files
2025-01-10 added high resolution and multi turn support
2025-01-10 mitsubishi encoder documentation
2025-01-10 renamed internal variable rev to revolutions
